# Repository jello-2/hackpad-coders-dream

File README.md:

# Coder's Dream
A 3 key macropad for Hackpad V2. Equipped with a 0.96" OLED screen. Created to be a Coder's Dream -- you'll only need the Ctrl, C, and V keys.

# BOM
- 3x Cherry MX Switches
- 1x SSD1036 OLED 128x64 0.96"
- 2x 4.7K Through-hole Resistors
- 1x XIAO RP2040
- 1x PCB

# Fully Assembled Macropad

# PCB

# Schematics

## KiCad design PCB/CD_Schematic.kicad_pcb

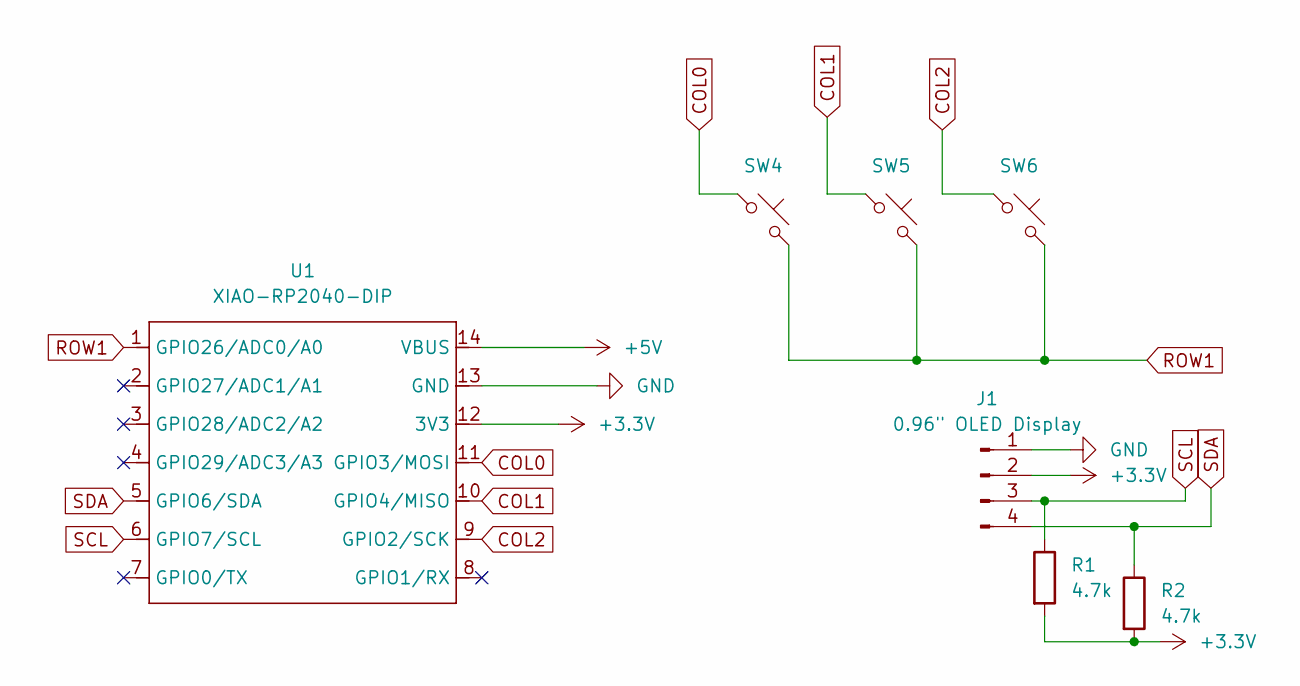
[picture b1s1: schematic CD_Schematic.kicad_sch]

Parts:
J1: 0.96" OLED Display; MODULE_DM-OLED096-636
R1, R2: 4.7k; R_Axial_DIN0204_L3.6mm_D1.6mm_P5.08mm_Horizontal
SW4, SW5, SW6: MX; SW_Cherry_MX_1.00u_PCB
U1: XIAO-RP2040-DIP

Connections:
+3.3V: J1.2, R1.2, R2.2, U1.12 (3V3)
+5V: U1.14 (VBUS)
COL0: SW4.1, U1.11 (GPIO3/MOSI)
COL1: SW5.1, U1.10 (GPIO4/MISO)
COL2: SW6.1, U1.9 (GPIO2/SCK)
GND: J1.1, U1.13 (GND)
ROW1: SW4.2, SW5.2, SW6.2, U1.1 (GPIO26/ADC0/A0)
SCL: J1.3, R1.1, U1.6 (GPIO7/SCL)
SDA: J1.4, R2.1, U1.5 (GPIO6/SDA)

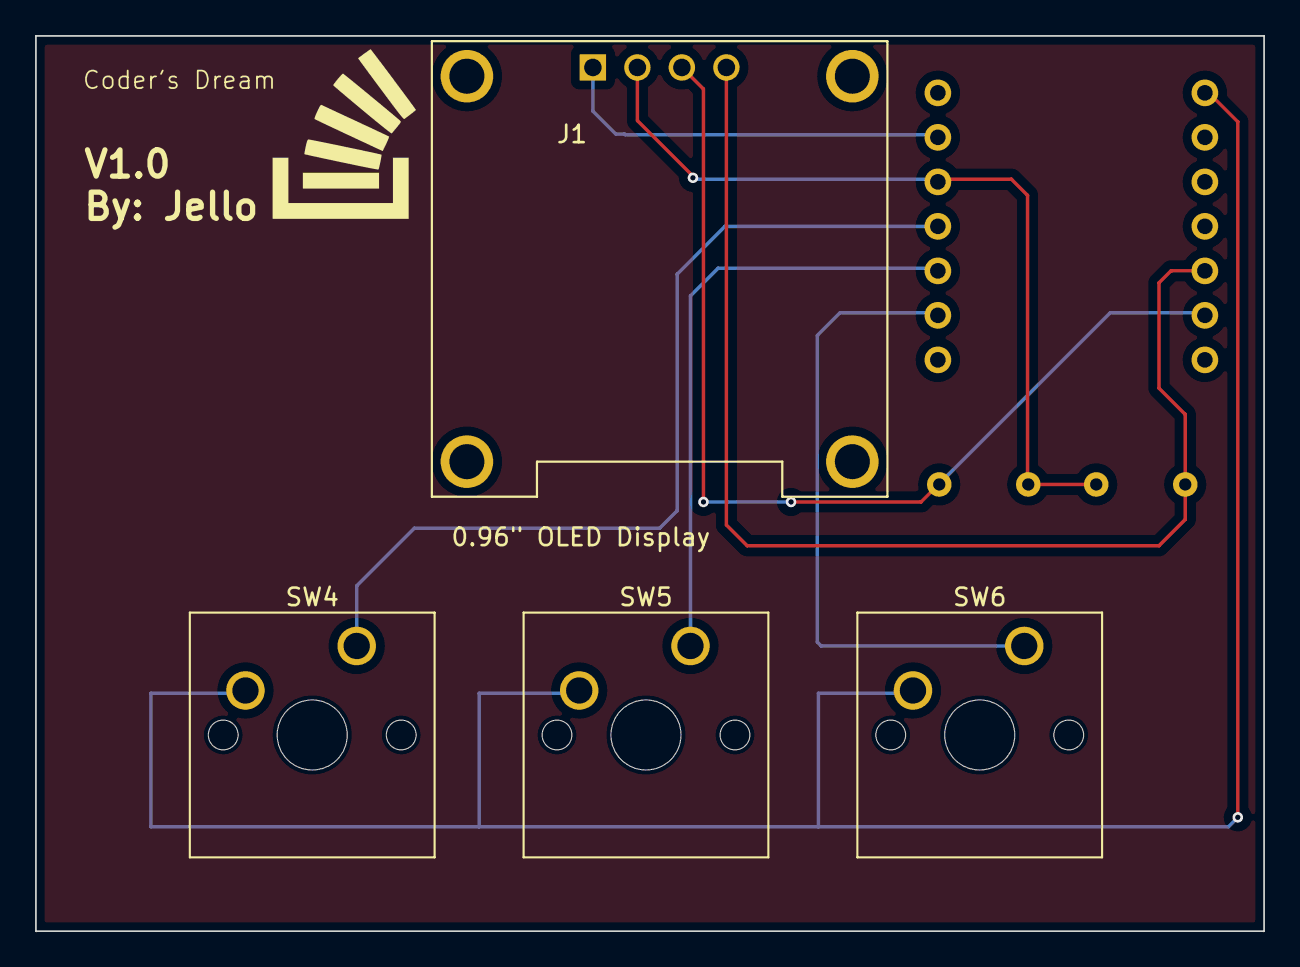
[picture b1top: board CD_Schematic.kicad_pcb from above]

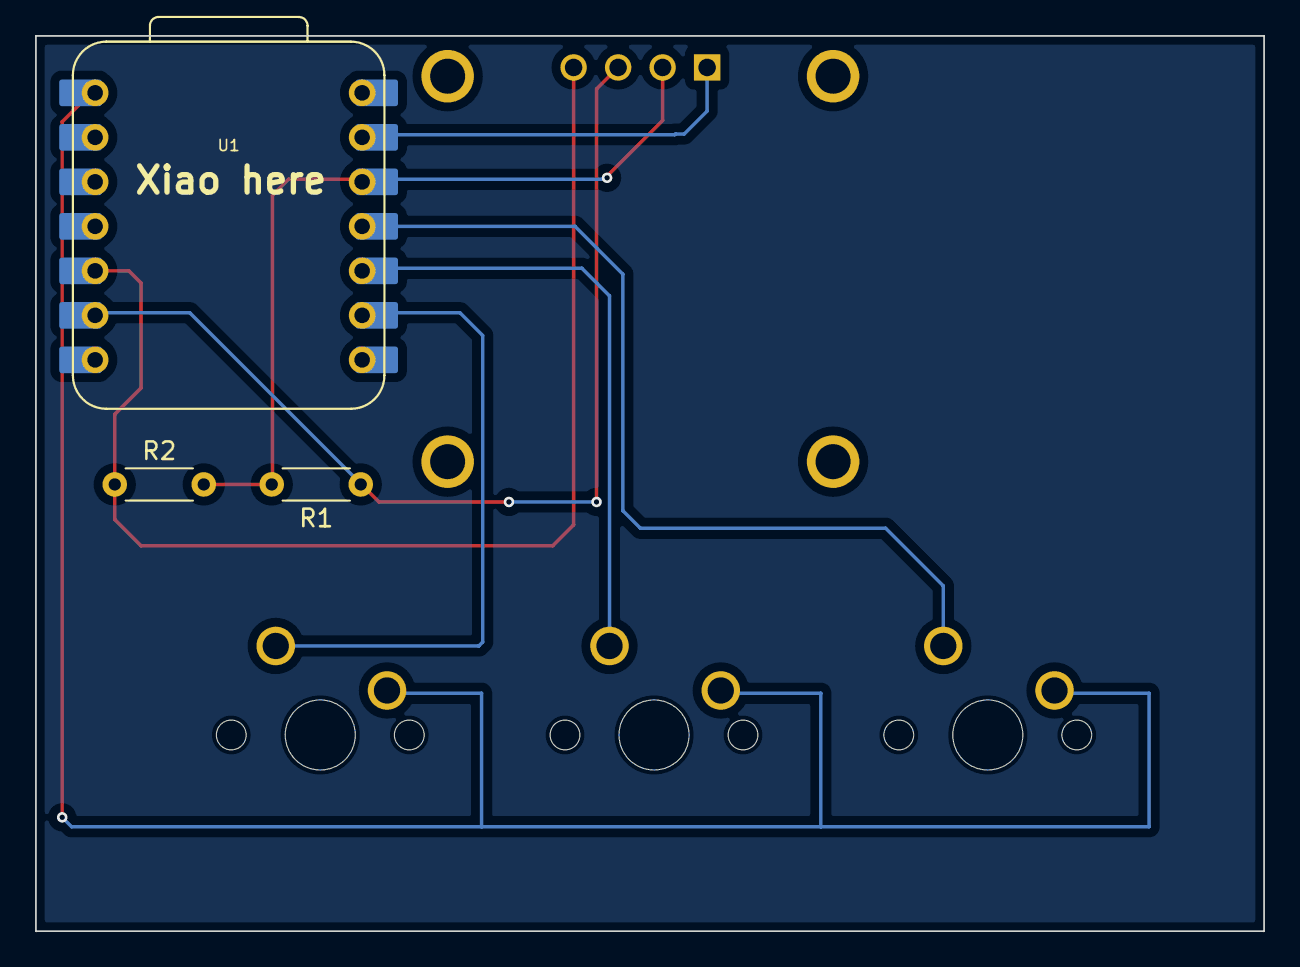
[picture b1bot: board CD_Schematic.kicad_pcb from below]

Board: 2 copper layers, 70.1 x 51.1 mm, 7 parts (3 on the bottom side), 8 nets.

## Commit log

2025-02-10 Created folders
2025-02-10 changed case design filet
2025-02-10 changed pcb
    pcb was missing (I didnt ground the switches ?) so i fixed it
2025-02-10 added firmware
2025-02-10 added compiled code
